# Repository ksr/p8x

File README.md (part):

# P8X — Hand-Built 8-Bit TTL CPU

A from-scratch 8-bit CPU built from ~130 74HCT logic chips on an 8-slot DIN41612 backplane. Fully microcoded; the microcode ROM images burned to the EPROMs are the same images the emulator interprets.

The machine now exists **twice**: as the TTL card set, and as an [FPGA
implementation](fpga/) of the same microarchitecture that boots the same
unmodified monitor, OS and toolchain. Both run the microcode from
`microcode/genucode.py`, and the C emulator is the golden reference for both.

The FPGA build also carries a **PGC-class graphics engine** (480x272
RGB565 panel, hardware 3D transforms, command lists, a fabric-parsed
graphics language modeled on the Matrox PG-640A) — see the
[theory of operation](docs/p8x-graphics-theory.md) and the
[graphics programmer's guide](docs/p8x-graphics-guide.md).

New to the abbreviations and signal names? See [GLOSSARY.md](GLOSSARY.md).

**Who made it:** I designed P8X, and it runs on an FPGA. Claude, Anthropic's AI, has been directly involved in its design, coding and documentation. — Ken Rother

## Architecture

- **8-bit data bus, 16-bit address bus**
- **4 × 16-bit pointer registers** (74169 up/down counters): P0 = PC, P1/P2 = general-purpose, P3 = stack pointer (empty-descending). The address bus is *always* driven by one of these — no separate MAR.
- **Registers:** A, B (ALU operands), T/T2 (hidden microcode temporaries), FLAGS (C, Z, N, V)
- **ALU:** 2 × 74181 + 74182 carry-lookahead, with a post-ALU shifter
- **Microcoded control:** 4 × 28C64 EEPROMs; ROM address = IR | step<<8 | cond<<12; **143 opcodes** defined in `microcode/genucode.py` (256 encodings available)
- **Memory map (rev E):** `$0000–$17FF` ROM (6 KB; shrunk from 8 KB 2026-09-14), `$1800–$FEFF` RAM (2× 62256; $1800–$1FFF is a scratch island), `$FF00–$FFFF` I/O (every data address is single-sourced in [`generators/gen_memmap.py`](generators/gen_memmap.py) → `memmap.inc`/`.h`/`.py`; commands pull the scratch/graphics/TPA-base symbols via `//#use mem`)

## Cards

The TTL machine is six core cards plus a PS/2 input card on the backplane, and a
bus test card for bring-up. Every board is designed and routed in **KiCad** (4-layer;
the plug-in cards are 280 × 140 mm) with orderable Gerbers in `hardware/<board>/kicad/`;
none has been fabricated yet. See [hardware/KICAD-BOARDS.md](hardware/KICAD-BOARDS.md)
and [hardware/RECONCILIATION.md](hardware/RECONCILIATION.md) (build readiness).

| Card | Function |
|------|----------|
| Control / Microcode | Clock, reset, sequencer, microcode EPROMs, IR, condition mux, front-panel |
| Register Bank | P0–P3 16-bit pointer registers, address bus drivers |
| ALU | A, B, T, T2 registers; 74181 ALU; shifter; FLAGS |
| Memory | 28C256 EEPROM (6 KB ROM window) + 2× 62256 SRAM, address decode (rev F) |
| I/O | Switches, LEDs, bus monitor, two 6850 ACIAs (RS-232, two DB9s) |
| CF-IDE | Two CompactFlash drives in 8-bit True IDE mode, at $FF10–$FF17 and $FF18–$FF1F |
| PS/2 | Keyboard + mouse ports at $FF58–$FF5F; an ATmega1284P behind a latch bridge |
| Bus test | Bring-up tool: a Raspberry Pi Pico drives the bus one microcycle at a time over USB |

The cards plug into a passive 8-slot backplane over a 96-pin DIN 41612 bus (rev C2).
The Eagle CAD of the first board generation is frozen (rev E) in each board's
`eagle-deprecated/` directory.

## Toolchain

| Tool | Location | Purpose |
|------|----------|---------|
| `microcode/genucode.py` | `microcode/` | Microcode generator → `u0–u3.bin` EPROM images |
| `assembler/p8xasm.py` | `assembler/` | Two-pass assembler, shares opcode table with genucode.py |
| `emulator/p8xemu.c` | `emulator/` | Cycle-accurate emulator, interprets the same u0–u3.bin images |
| `firmware/p8xmon.asm` | `firmware/` | ROM monitor (E/D/I/F/B/G/? commands) + BIOS jump table at `$0100` |
| `os/p8xos.asm` | `os/` | P8X/OS, RAM-resident disk OS booted from CF ([guide](os/README.md)) |
| `tools/p8xfs.py` | `tools/` | Host-side P8XFS disk-image tool (create/boot/put/get/ls) |
| `basic/p8xbasic.asm` | `basic/` | BASIC interpreter — disk-bootable or run-from-OS builds ([guide](basic/README.md)) |
| `apps/p8xedit.asm`, `apps/p8xasm.asm`, `apps/p8xcc.asm` | `apps/` | On-target toolchain: line editor + native two-pass assembler + native C compiler (`cc`), as `/bin` programs ([guide](apps/README.md)) |
| `compiler/p8cc.py` | `compiler/` | C cross-compiler (subset) → P8X asm → RUNnable `.bin` ([guide](compiler/README.md)) |
| `generators/gen_p8xopc.py` | `generators/` | Opcode table for the native assembler, generated from `genucode.OPC` |
| `generators/gen_eagle.py` | `generators/` | The canonical board netlists (`CARDS`, `busnet()`); its Eagle output is frozen at rev E |
| `generators/gen_kicad.py`, `build.sh` | `generators/` | KiCad boards from those netlists: placement, Freerouting, Gerbers, and the ERC/DRC readiness check |

**Generators are canon.** Never hand-edit board files (`.kicad_pcb`, and the frozen Eagle `.sch`/`.brd`) or ROM binaries — they are build artifacts. Edit the generator and regenerate. See [generators/README.md](generators/README.md) for what each script does and how to run it.

## Quick Start

Setting up a new machine? See [SETUP.md](SETUP.md) for the full toolchain, tier by
tier, and run `python3 tools/setup_check.py` to see what is installed and what each
work area still needs. Only the core-software tier is required to build and test.

```sh
# Build the emulator and regenerate microcode images
cd emulator && make

# Run the smoke tests (message print, JSR/RTS round-trip, branch countdown)
make test

# Rebuild a KiCad board: placement -> Freerouting -> Gerbers + renders -> the
# ERC/gate-sim/DRC/keepout/fab readiness check (needs KiCad 10 and a Freerouting
# jar; `all` builds every board). The netlists come from generators/gen_eagle.py.
cd ..
sh generators/build.sh memory-card
sh generators/check_card.sh memory-card          # the readiness check alone

# Reference PDFs (run from anywhere):
cd hardware
python3 ../generators/gen_bus_pdf.py              # bus definition PDF (hardware/backplane/)
python3 ../microcode/gen_progguide.py             # programmer's guide (-> docs/)
```

### EEPROM / programmer images

Both build paths emit **Intel HEX** alongside the raw `.bin`, for loading into an
EEPROM programmer:

- **Microcode** — `microcode/genucode.py` writes `u0–u3.bin` (what the emulator
  and tests load); the matching Intel HEX for the four 28C64 control-store EPROMs
  is produced into `rom/` by `make rom` (see below).
- **Program ROM** — the assembled monitor + BIOS for the 28C256 at `$0000`
  (about 4.9 KB of the 6 KB window; BASIC is no longer ROM-resident). `make rom` builds it into `rom/`.
- **Any other binary** — `python3 tools/bin2hex.py in.bin out.hex [base]`
  (e.g. a monitor built directly with `p8xasm.py`).

For a ready-to-burn set at fixed paths, run `cd emulator && make rom` (or
`sh tools/build_rom.sh`). It refreshes the four control-store EPROMs in
`microcode/` and writes the program ROM to `rom/p8x-prog-rom.{bin,hex}`. Both
are committed; see [rom/README.md](rom/README.md) for the chip map.

## Documentation

The documents below are also built into the project website, [p8x.cottageworker.com](https://p8x.cottageworker.com) (`website/`, MkDocs; published on every push to `main`).

| Document | Description |
|----------|-------------|
| [hardware/backplane/p8x-bus-definition.md](hardware/backplane/p8x-bus-definition.md) | Authoritative 96-pin bus pinout, signal descriptions, DOE/DLD encoding, microcode word layout |
| [hardware/backplane/p8x-backplane-design.md](hardware/backplane/p8x-backplane-design.md) | PCB stackup, termination analysis, BOM |
| [docs/p8x-card-standards.md](docs/p8x-card-standards.md) | Design rules that apply to every plug-in card |
| [docs/p8x-system-design.md](docs/p8x-system-design.md) | System and card-by-card architecture reference |
| [hardware/cf-card/p8x-cf-os-design.md](hardware/cf-card/p8x-cf-os-design.md) | CF-IDE hardware + P8X/OS design |
| [hardware/cf-card/p8xfs-v2-hierarchical.md](hardware/cf-card/p8xfs-v2-hierarchical.md) | P8XFS v2 hierarchical filesystem spec |
| [docs/p8x-programmers-guide.pdf](docs/p8x-programmers-guide.pdf) | Generated instruction set reference |
| [basic/p8x-basic-guide.md](basic/p8x-basic-guide.md) | P8X BASIC language reference (statements, expressions, graphics, examples) |
| [fpga/README.md](fpga/README.md) | FPGA build: milestones, getting started, both paths |
| [fpga/docs/architecture.md](fpga/docs/architecture.md) | FPGA module hierarchy, peripheral map, graphics, co-sim spec |
| [fpga/rtl/README.md](fpga/rtl/README.md) | What is shared vs sim-only, and the `cen` / `sc_en` contracts |
| [fpga/sim/README.md](fpga/sim/README.md) | How the co-sim trace-diff works, and the graphics frame diff |
| [BACKLOG.md](BACKLOG.md) | Live work only: NEXT / IDEAS / VERIFY / WONT-DO |
| [BACKLOG-DONE.md](BACKLOG-DONE.md) | Completed work + the project log |

### Per-card guides

Each board has its own directory under `hardware/` holding everything about it —
the KiCad board and its Gerbers, placement PDF and renders (`kicad/`), a README
explaining how the circuit works chip by chip, any board-specific design docs, and
the frozen Eagle files (`eagle-deprecated/`):

| Card | Directory |
|------|-----------|
| Control / Microcode | [hardware/control-card/](hardware/control-card/README.md) |
| Register Bank | [hardware/regbank-card/](hardware/regbank-card/README.md) |
| ALU | [hardware/alu-card/](hardware/alu-card/README.md) |
| Memory | [hardware/memory-card/](hardware/memory-card/README.md) |
| I/O | [hardware/io-card/](hardware/io-card/README.md) |
| CF-IDE | [hardware/cf-card/](hardware/cf-card/README.md) |
| PS/2 | [hardware/ps2-card/](hardware/ps2-card/README.md) |
| Bus test | [hardware/bustest-card/](hardware/bustest-card/p8x-bustest-card-design.md) |
| Backplane | [hardware/backplane/](hardware/backplane/p8x-backplane-design.md) |

## FPGA implementation

A standalone [FPGA build](fpga/) on a **Sipeed Tang Nano 20K** (Gowin GW2AR-18)
runs the whole machine — CPU, memory, ACIA console, microSD disk, and a 4.3"
480x272 graphics panel — from one chip and a USB cable. It is a **parallel track to the TTL build, not a replacement**:
same horizontal microcode word, same sequencer, same pointer/address model, so
the monitor, OS, BASIC, C compiler and assembler run **unmodified**.

| Milestone | State |
|-----------|-------|
| 0 First light (UART echo + heartbeat) | done |
| 1 CPU core in simulation, all 88 opcodes of the time | done |
| 2 ACIA + driven console in simulation | done |
| 3 Core on real hardware, full 64K map | done |
| 4 microSD disk — P8X/OS boots from card | done |
| 5 Clock-up + IRQ | next |
| 6 Graphics: 480x272 panel + drawing engine | done |

As built: **9 MHz** effective (27 MHz fabric, three phases per microcycle). The
CPU-only build is 40/46 block RAMs at ~48 MHz Fmax; adding the graphics panel takes
it to 44/46 and 13288/20736 LUT4, with Fmax measured at 38.8 MHz — still four times
the clock it runs at. P8X is programmed into the board's flash, so it comes up
standalone on power.

**Graphics** (`build.sh lcd`) adds the panel's native 480×272 framebuffer in
**RGB565 direct colour** — a pixel IS its colour, 65,536 of them — living in
the Tang Nano's in-package SDRAM behind a streaming controller, with a drawing
engine driven by BASIC in one window-space coordinate system (y up, the
PGC's own): `COLOR r,g,b` (or one packed value), `CLS`, `PIXELW`, `LINE`,
`BOX`, `CIRCLE` (a second radius gives an ellipse), `IMAGE` (draws a
P8I picture file — `tools/p8img.py` converts anything into one), the
`PIXELR(x,y)` and `RGB(r,g,b)` functions — plus the full PGC graphics
language as native statements (`MOVE`/`DRAW`/`POLY`/`RECT`, matrices, 3D,
command lists; see `man basic`). Text is the PGC's own stroke `TEXT`,
drawn card-side from the font the OS streams from `/FONT.GL` at boot
(GTEXT and its software rasterizer retired 2026-09-01). The drawing
statements emit that language; the engine lives in the device, so a
filled box costs the same handful of instructions as an empty one.
There is one geometry and no modes or palette to manage.
The same device is modelled in `p8xemu`, and the two are byte-compared frame
by frame.

**3D** (stages 7–8, `fpga/tang-nano-20k/sdram/STAGE*.md`): a wireframe
pipeline available three ways from C — all in software (`//#use gfx` +
`//#use g3d`), accelerated by the **MDU** (a memory-mapped hardware
multiply-divide unit at `$FF30`), or fully in fabric via the **geometry
engine** (`$FF40`): edge lists in SDRAM, an S7.8 matrix, one command to
transform/clip/project/draw, and page-flipped double buffering. The same
program picks the fastest fitted path at runtime; `cube` on the shipped disk
demonstrates all of them (`man cube`, `man g3d`).

**Verification is the point.** Every milestone is "make the RTL match the
emulator": the same program runs on both and their per-cycle architectural state
is diffed, so a divergence is a bug with an exact microcycle and signal rather
than a mystery. `fpga/sim/isa_test.asm` drives the original 88 opcodes through that diff;
the 55 added since are microcode only (no new hardware), and the RTL runs them from
the same images.

```sh
fpga/sim/run.sh 60000 isa_test.asm          # co-sim, the original 88 opcodes
fpga/sim/console.sh "" os/run-disk.img      # interactive console on the RTL
fpga/tang-nano-20k/build.sh cpu load        # build + program the board
```

## Status

- Emulator working: 143 opcodes, ACIA on stdin/stdout, CF-IDE disk model (`-c `), interactive I/O card (switches `-s`, LED trace `-L`), verified against microcode images
- Assembler working: two-pass, full expression support, shares opcode table with microcode generator
- KiCad boards designed and routed for the six CPU cards, the PS/2 card, the bus test card and the backplane (9 boards, 0 unconnected, Gerbers in each `kicad/`); none fabricated yet. The Eagle files of the first generation are frozen in `eagle-deprecated/`. (The standalone LED test card was a CAD-workflow trial, never built — deprecated and moved to `hardware/deprecated/led-card/`; its I/O address `$FF0C` is now free.)
- ROM monitor boots in the emulator; its filesystem hooks (`I`/`F`/`B`) run end to end against a CF image (`make test-cf`)
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
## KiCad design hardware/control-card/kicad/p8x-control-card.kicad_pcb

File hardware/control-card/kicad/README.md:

# control-card -- KiCad

Generated by `generators/gen_kicad.py` from the canonical gen_eagle netlist
(`CARDS["control-card"]`), same standard as the memory card: 4-layer (F/B signals,
In1=GND, In2=VCC planes), a bypass cap above each IC, a labelled LED/jumper bank,
part values on silk. Routed with Freerouting. GENERATORS ARE CANON -- edit
`gen_kicad.py` and re-run `generators/build_kicad_card.sh control-card`.

| File | What |
|------|------|
| `p8x-control-card.kicad_pcb` | the board |
| `p8x-control-card.ses` | the Freerouting routing |
| `p8x-control-card-gerbers.zip` | orderable gerbers |
| `p8x-control-card-placement.pdf` | parts placement (refs+values) |
| `p8x-control-card-render-top.png` / `-3d.png` | renders |

Exotic parts use the closest standard KiCad footprint (flagged when built).

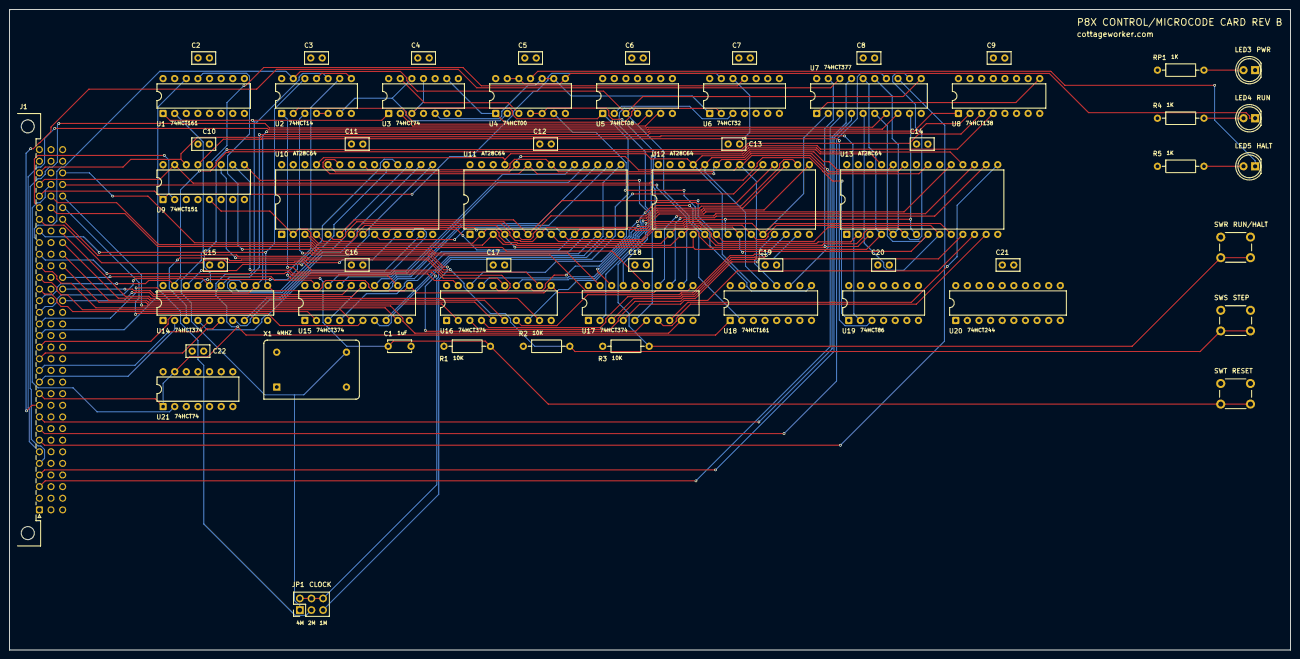
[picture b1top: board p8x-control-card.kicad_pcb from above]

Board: 4 copper layers, 280.0 x 140.0 mm, 58 parts (0 on the bottom side), 120 nets.

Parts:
C1: 1uF; C_Disc_D5.0mm_W2.5mm_P5.00mm
C2, C3, C4, C5, C6, C7, C8, C9, C10, C11, C12, C13, C14, C15, C16, C17, C18, C19, C20, C21, C22: 100nF; C_Disc_D5.0mm_W2.5mm_P2.50mm
J1: MABC96R; DIN41612_C_3x32_Male_Horizontal_THT
JP1: CLKSEL; PinHeader_2x03_P2.54mm_Vertical
LED3, LED4: GRN; LED_D5.0mm
LED5: RED; LED_D5.0mm
R1, R2, R3: 10K; R_Axial_DIN0207_L6.3mm_D2.5mm_P10.16mm_Horizontal
R4, R5: 1K; R_Axial_DIN0207_L6.3mm_D2.5mm_P10.16mm_Horizontal
RP1: 1K; R_Axial_DIN0207_L6.3mm_D2.5mm_P10.16mm_Horizontal
SWR: SPST; SW_PUSH_6mm
SWS: SPST; SW_PUSH_6mm
SWT: SPST; SW_PUSH_6mm
U1, U18: 74HCT161; DIP-16_W7.62mm
U2: 74HCT14; DIP-14_W7.62mm
U3, U21: 74HCT74; DIP-14_W7.62mm
U4: 74HCT00; DIP-14_W7.62mm
U5: 74HCT08; DIP-14_W7.62mm
U6: 74HCT32; DIP-14_W7.62mm
U7: 74HCT377; DIP-20_W7.62mm
U8: 74HCT138; DIP-16_W7.62mm
U9: 74HCT151; DIP-16_W7.62mm
U10, U11, U12, U13: 28C64; DIP-28_W15.24mm
U14, U15, U16, U17: 74HCT374; DIP-20_W7.62mm
U19: 74HCT86; DIP-14_W7.62mm
U20: 74HCT244; DIP-20_W7.62mm
X1: 4MHZ; Oscillator_DIP-14

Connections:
-IRLD: U7.1, U8.9
-RES: J1.a11, U1.1, U2.10, U3.1, U18.1, U21.1, U21.13
-USTL: U4.6, U18.9
ALUM: J1.c23, U16.5
ALUS0: J1.c19, U15.15
ALUS1: J1.c20, U15.16
ALUS2: J1.c21, U15.19
ALUS3: J1.c22, U16.2
BSEL: J1.b28, U17.19
CIN: J1.c24, U16.6
CLK: J1.a24, U2.13, U5.3, U7.11, U18.2
CLKB: J1.a25, U2.12, U14.11, U15.11, U16.11, U17.11
CLKEN: U5.2, U6.3
CLKRAW: JP1.2, JP1.4, JP1.6, U3.3, U3.11, U5.1
CLRC: J1.b27, U17.16
CONDY: U9.5, U10.2, U11.2, U12.2, U13.2
D0: J1.a3, U7.3
D1: J1.a4, U7.4
D2: J1.a5, U7.7
D3: J1.a6, U7.8
D4: J1.a7, U7.13
D5: J1.a8, U7.14
D6: J1.a9, U7.17
D7: J1.a10, U7.18
DIVQA: JP1.3, U1.14
DIVQB: JP1.5, U1.13
DLD0: J1.a16, U8.1, U14.12
DLD1: J1.a17, U8.2, U14.15
DLD2: J1.a18, U8.3, U14.16
DLD3: J1.a19, U8.4, U14.19
DOE0: J1.a12, U14.2
DOE1: J1.a13, U14.5
DOE2: J1.a14, U14.6
DOE3: J1.a15, U14.9
FC: J1.a27, U9.2
FCOND0: U9.11, U16.16
FCOND1: U9.10, U16.19
FCOND2: U9.9, U17.2
FN: J1.a29, U9.15, U19.1
FV: J1.a30, U9.14, U19.2
FZ: J1.a28, U6.13, U9.1
GND: C1.2, C2.2, C3.2, C4.2, C5.2, C6.2, C7.2, C8.2, C9.2, C10.2, C11.2, C12.2, C13.2, C14.2, C15.2, C16.2, C17.2, C18.2, C19.2, C20.2, C21.2, C22.2, J1.a31, J1.a32, J1.b3, J1.b5, J1.b7, J1.b9, J1.b11, J1.b13, J1.b15, J1.b17, J1.b19, J1.b21, J1.b23, J1.b25, J1.b31, J1.b32, J1.c31, J1.c32, LED3.1, SWR.1, SWS.1, SWT.1, U1.3, U1.4, U1.5, U1.6, U1.8, U2.7, U3.7, U4.7, U5.7, U5.9, U5.10, U5.12, U5.13, U6.4, U6.5, U6.7, U6.9, U6.10, U7.10, U8.5, U8.8, U9.4, U9.7, U9.8, U10.14, U10.20, U10.22, U11.14, U11.20, U11.22, U12.14, U12.20, U12.22, U13.14, U13.20, U13.22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
HALT: U2.1, U17.6
HALTK: LED5.1, U4.11
HALTN: U2.2, U5.5
IRQ: J1.b29, U21.2
IRQ0: U7.2, U10.10, U11.10, U12.10, U13.10
IRQ1: U7.5, U10.9, U11.9, U12.9, U13.9
IRQ2: U7.6, U10.8, U11.8, U12.8, U13.8
IRQ3: U7.9, U10.7, U11.7, U12.7, U13.7
IRQ4: U7.12, U10.6, U11.6, U12.6, U13.6
IRQ5: U7.15, U10.5, U11.5, U12.5, U13.5
IRQ6: U7.16, U10.4, U11.4, U12.4, U13.4
IRQ7: U7.19, U10.3, U11.3, U12.3, U13.3
LDF: J1.a26, U16.15
LDZN: J1.c28, U17.9
LEDHL: LED5.2, R5.2
LEDP: LED3.2, RP1.2
LEDRN: LED4.2, R4.2
NV: U6.12, U9.13, U19.3
NVZ: U6.11, U9.12
OSCO: JP1.1, U1.2, X1.8
P14B0: U10.11, U14.3
P14B1: U10.12, U14.4
P14B2: U10.13, U14.7
P14B3: U10.15, U14.8
P14B4: U10.16, U14.13
P14B5: U10.17, U14.14
P14B6: U10.18, U14.17
P14B7: U10.19, U14.18
P15B0: U11.11, U15.3
P15B1: U11.12, U15.4
P15B2: U11.13, U15.7
P15B3: U11.15, U15.8
P15B4: U11.16, U15.13
P15B5: U11.17, U15.14
P15B6: U11.18, U15.17
P15B7: U11.19, U15.18
P16B0: U12.11, U16.3
P16B1: U12.12, U16.4
P16B2: U12.13, U16.7
P16B3: U12.15, U16.8
P16B4: U12.16, U16.13
P16B5: U12.17, U16.14
P16B6: U12.18, U16.17
P16B7: U12.19, U16.18
P17B0: U13.11, U17.3
P17B1: U13.12, U17.4
P17B2: U13.13, U17.7
P17B3: U13.15, U17.8
P17B4: U13.16, U17.13
P17B5: U13.17, U17.14
P17B6: U13.18, U17.17
P17B7: U13.19, U17.18
PDEC: J1.a23, U15.12
PINC: J1.a22, U15.9
PSEL0: J1.a20, U15.2
PSEL1: J1.a21, U15.5
PSEL2: J1.c27, U15.6
RSTP: U2.8, U2.11
RSTRAW: C1.1, R1.2, SWT.2, U2.9
RUND: U3.2, U5.6
RUNLK: LED4.1, U4.8, U4.12, U4.13
RUNQ: U3.5, U4.9, U4.10, U6.1
RUNSW: R3.2, SWR.2, U5.4
SETC: J1.c30, U17.15
SH0: J1.c25, U16.9
SH1: J1.c26, U16.12
SHCIN: J1.c29, U17.12
SQ0: U10.25, U11.25, U12.25, U13.25, U18.14
SQ1: U10.24, U11.24, U12.24, U13.24, U18.13
SQ2: U10.21, U11.21, U12.21, U13.21, U18.12
SQ3: U10.23, U11.23, U12.23, U13.23, U18.11
STEPCLR: U3.13, U4.3
STEPN: U2.4, U2.5
STEPP: U2.6, U3.12, U4.2
STEPQ: U3.9, U4.1, U6.2
STEPRAW: R2.2, SWS.2, U2.3
URST: U4.4, U4.5, U17.5
VCC: C2.1, C3.1, C4.1, C5.1, C6.1, C7.1, C8.1, C9.1, C10.1, C11.1, C12.1, C13.1, C14.1, C15.1, C16.1, C17.1, C18.1, C19.1, C20.1, C21.1, C22.1, J1.a1, J1.a2, J1.b1, J1.b2, J1.c1, J1.c2, R1.1, R2.1, R3.1, R4.1, R5.1, RP1.1, U1.7, U1.9, U1.10, U1.16, U2.14, U3.4, U3.10, U3.14, U4.14, U5.14, U6.14, U7.20, U8.6, U8.16, U9.3, U9.16, U10.27, U10.28, U11.27, U11.28, U12.27, U12.28, U13.27, U13.28, U14.20, U15.20, U16.20, U17.20, U18.7, U18.10, U18.16, U19.14, U20.1, U20.8, U20.19, U20.20, U21.4, U21.10, U21.14, X1.14

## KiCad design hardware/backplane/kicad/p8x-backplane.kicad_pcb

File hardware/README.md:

# hardware/

The physical machine: one passive backplane, six plug-in CPU cards, a PS/2 input
card, and a bus test card for bring-up. Each board has its own directory holding a
chip-by-chip README, a theory of operation or design doc, and the **KiCad** board
(`kicad/`: the `.kicad_pcb`, the Freerouting session, orderable Gerbers, a
placement PDF and renders). Every board is designed and routed; none has been
fabricated yet. Board status: **[KICAD-BOARDS.md](KICAD-BOARDS.md)**; build
readiness against the emulator and the FPGA: **[RECONCILIATION.md](RECONCILIATION.md)**.

| Board | Directory | Function |
|-------|-----------|----------|
| Control / Microcode | [control-card/](control-card/README.md) | Clock, reset, sequencer, microcode EPROMs, IR, condition mux, front panel |
| Register Bank | [regbank-card/](regbank-card/README.md) | P0–P3 16-bit pointer registers, address-bus drivers |
| ALU | [alu-card/](alu-card/README.md) | A/B/T/T2 registers, 74181 ALU, shifter, FLAGS |
| Memory | [memory-card/](memory-card/README.md) | 28C256 ROM (6 KB window, `$0000–$17FF`) + 2× 62256 SRAM, address decode (rev F) |
| I/O | [io-card/](io-card/README.md) | Switches, LEDs, bus monitor, two 6850 ACIAs (`$FF04/05`, `$FF08/09`) with two DB9s (rev B) |
| CF-IDE | [cf-card/](cf-card/README.md) | Two CompactFlash drives in 8-bit True IDE mode: `$FF10–$FF17` and `$FF18–$FF1F` (rev B) |
| PS/2 | [ps2-card/](ps2-card/README.md) | Keyboard + mouse at `$FF58–$FF5F`: an ATmega1284P behind a latch bridge (rev A) |
| Bus test | [bustest-card/](bustest-card/p8x-bustest-card-design.md) | Bring-up tool: a Raspberry Pi Pico drives the bus over USB, one microcycle at a time |
| Backplane | [backplane/](backplane/p8x-backplane-design.md) | 8-slot passive 96-pin DIN 41612 bus (rev C2), 262 × 128 mm |

The plug-in cards are all 280 × 140 mm, 4-layer (signals on the outer layers, GND
and +5 V planes inside).

**Eagle (frozen).** The first board generation was drawn in Eagle/Fusion from
`generators/gen_eagle.py`. On 2026-09-18 the KiCad flow replaced it: each board's
Eagle `.sch`/`.brd` and its schematic and placement PDFs moved to
`<board>/eagle-deprecated/`, frozen at rev E, and are no longer maintained (the
Eagle memory card still carries the old 8 KB ROM decode; the KiCad rev F board has
the 6 KB one). `gen_eagle.py` stays the source of the netlists.

> **Deprecated:** the standalone **LED test card** (a write-only 8-LED output
> latch that decoded `$FF0C`) was a CAD-workflow trial, never built. It has been
> moved to [`deprecated/led-card/`](deprecated/led-card/) and its I/O address
> `$FF0C` is now free. (This is unrelated to the `$FF02` LED latch the emulator
> traces, which stays.) The combined I/O + CF + PS/2 **peripheral card** is parked
> in `parked/peripheral-card/` (2026-09-19); the design went back to three cards.

### Not yet realised as TTL boards
See **[RECONCILIATION.md](RECONCILIATION.md)** for the full board-vs-emulator/FPGA
build-readiness pass. Subsystems the emulator and/or the FPGA already provide that
have **no TTL card** yet:

| Subsystem | Where it lives now | TTL board |
|-----------|--------------------|-----------|
| MDU multiply/divide (`$FF30–$FF3F`) | emulator model + FPGA (`mdu_core.v`) | none yet |
| Graphics-language port (`$FF50–$FF54`) | emulator model + the Tang Nano 20K graphics card | none (the FPGA card *is* the graphics engine) |
| IRQ controller (`$FF06` device-IRQ model) | emulator model | none yet — the next card to design |

**[assembly/](assembly/README.md)** — 3D renders of the assembled machine: the
backplane with all eight cards standing in their slots, each card populated
(rendered from the boards by `generators/render_assembly.py`; slot order inside).

`p8x-bom.csv` — the orderable bill of materials for the whole machine
(ICs, sockets, connectors, passives), generated by
[`../generators/gen_bom.py`](../generators/).

## Rebuilding boards

**Generators are canon** — never hand-edit a `.kicad_pcb`. The netlists live in
[`../generators/gen_eagle.py`](../generators/) (`CARDS`, `busnet()`);
`gen_kicad.py` turns a card into a placed KiCad board (the memory, I/O, CF, PS/2
cards and the backplane have bespoke placement scripts in their `kicad/`
directories), Freerouting routes it, and `check_card.sh` runs the readiness check
(ERC, gate-level simulation where a testbench exists, DRC, mounting-hole keepout,
fab minimums). One command does all of it, from the repository root:

```sh
sh generators/build.sh memory-card      # one board (or: all)
sh generators/check_card.sh memory-card # the readiness check alone
```

It needs KiCad 10 and a Freerouting jar. See
[../generators/README.md](../generators/README.md) for the scripts and
[../docs/p8x-card-standards.md](../docs/p8x-card-standards.md) for the rules
every card follows.

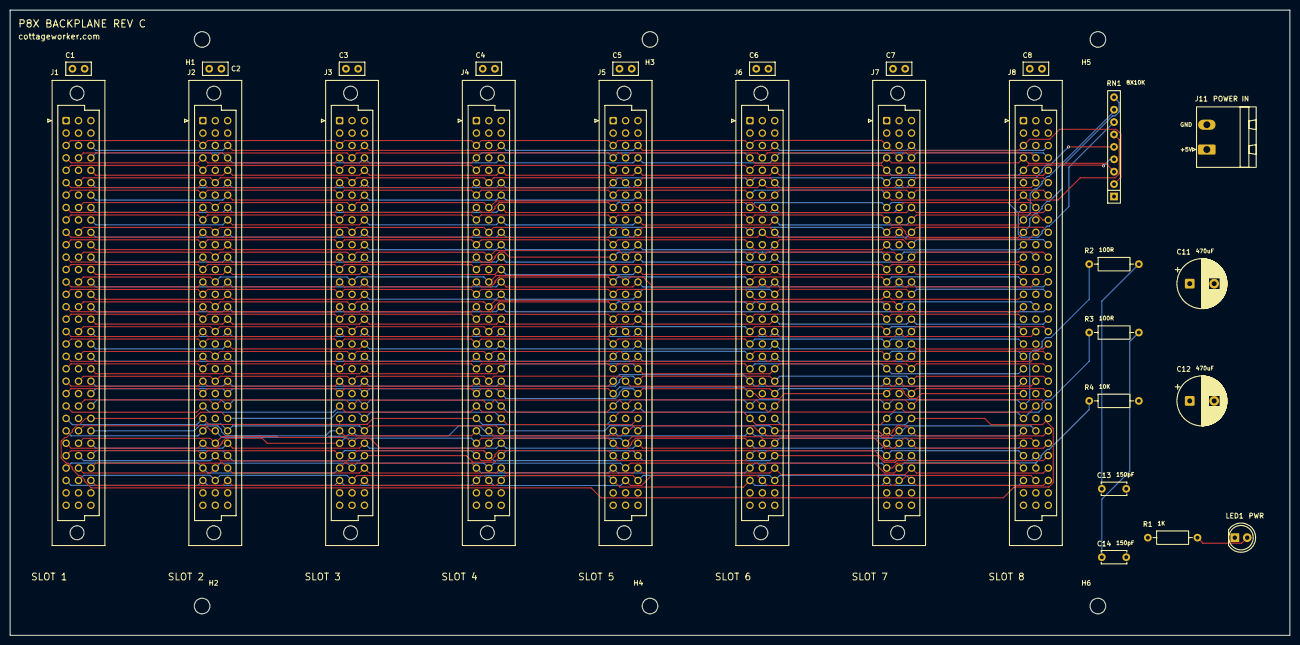
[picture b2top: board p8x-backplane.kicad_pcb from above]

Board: 4 copper layers, 262.0 x 128.0 mm, 33 parts (0 on the bottom side), 77 nets.

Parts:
C1, C2, C3, C4, C5, C6, C7, C8: 100nF; C_Disc_D5.0mm_W2.5mm_P2.50mm
C11, C12: 470uF; CP_Radial_D10.0mm_P5.00mm
C13, C14: 150pF; C_Disc_D5.0mm_W2.5mm_P5.00mm
H1, H2, H3, H4, H5, H6: MountingHole_3.2mm_M3
J1: SLOT1; DIN41612_C_3x32_Female_Vertical_THT
J2: SLOT2; DIN41612_C_3x32_Female_Vertical_THT
J3: SLOT3; DIN41612_C_3x32_Female_Vertical_THT
J4: SLOT4; DIN41612_C_3x32_Female_Vertical_THT
J5: SLOT5; DIN41612_C_3x32_Female_Vertical_THT
J6: SLOT6; DIN41612_C_3x32_Female_Vertical_THT
J7: SLOT7; DIN41612_C_3x32_Female_Vertical_THT
J8: SLOT8; DIN41612_C_3x32_Female_Vertical_THT
J11: PWR-5V; PhoenixContact_MSTBA_2,5_2-G-5,08_1x02_P5.08mm_Horizontal
LED1: PWR; LED_D5.0mm
R1: 1K; R_Axial_DIN0207_L6.3mm_D2.5mm_P10.16mm_Horizontal
R2, R3: 100R; R_Axial_DIN0207_L6.3mm_D2.5mm_P10.16mm_Horizontal
R4: 10K; R_Axial_DIN0207_L6.3mm_D2.5mm_P10.16mm_Horizontal
RN1: 8X10K; R_Array_SIP9

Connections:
-RES: J1.a11, J2.a11, J3.a11, J4.a11, J5.a11, J6.a11, J7.a11, J8.a11
A0: J1.c3, J2.c3, J3.c3, J4.c3, J5.c3, J6.c3, J7.c3, J8.c3
A1: J1.c4, J2.c4, J3.c4, J4.c4, J5.c4, J6.c4, J7.c4, J8.c4
A2: J1.c5, J2.c5, J3.c5, J4.c5, J5.c5, J6.c5, J7.c5, J8.c5
A3: J1.c6, J2.c6, J3.c6, J4.c6, J5.c6, J6.c6, J7.c6, J8.c6
A4: J1.c7, J2.c7, J3.c7, J4.c7, J5.c7, J6.c7, J7.c7, J8.c7
A5: J1.c8, J2.c8, J3.c8, J4.c8, J5.c8, J6.c8, J7.c8, J8.c8
A6: J1.c9, J2.c9, J3.c9, J4.c9, J5.c9, J6.c9, J7.c9, J8.c9
A7: J1.c10, J2.c10, J3.c10, J4.c10, J5.c10, J6.c10, J7.c10, J8.c10
A8: J1.c11, J2.c11, J3.c11, J4.c11, J5.c11, J6.c11, J7.c11, J8.c11
A9: J1.c12, J2.c12, J3.c12, J4.c12, J5.c12, J6.c12, J7.c12, J8.c12
A10: J1.c13, J2.c13, J3.c13, J4.c13, J5.c13, J6.c13, J7.c13, J8.c13
A11: J1.c14, J2.c14, J3.c14, J4.c14, J5.c14, J6.c14, J7.c14, J8.c14
A12: J1.c15, J2.c15, J3.c15, J4.c15, J5.c15, J6.c15, J7.c15, J8.c15
A13: J1.c16, J2.c16, J3.c16, J4.c16, J5.c16, J6.c16, J7.c16, J8.c16
A14: J1.c17, J2.c17, J3.c17, J4.c17, J5.c17, J6.c17, J7.c17, J8.c17
A15: J1.c18, J2.c18, J3.c18, J4.c18, J5.c18, J6.c18, J7.c18, J8.c18
ALUM: J1.c23, J2.c23, J3.c23, J4.c23, J5.c23, J6.c23, J7.c23, J8.c23
ALUS0: J1.c19, J2.c19, J3.c19, J4.c19, J5.c19, J6.c19, J7.c19, J8.c19
ALUS1: J1.c20, J2.c20, J3.c20, J4.c20, J5.c20, J6.c20, J7.c20, J8.c20
ALUS2: J1.c21, J2.c21, J3.c21, J4.c21, J5.c21, J6.c21, J7.c21, J8.c21
ALUS3: J1.c22, J2.c22, J3.c22, J4.c22, J5.c22, J6.c22, J7.c22, J8.c22
BSEL: J1.b28, J2.b28, J3.b28, J4.b28, J5.b28, J6.b28, J7.b28, J8.b28
CIN: J1.c24, J2.c24, J3.c24, J4.c24, J5.c24, J6.c24, J7.c24, J8.c24
CLK: J1.a24, J2.a24, J3.a24, J4.a24, J5.a24, J6.a24, J7.a24, J8.a24, R2.1
CLKB: J1.a25, J2.a25, J3.a25, J4.a25, J5.a25, J6.a25, J7.a25, J8.a25, R3.1
CLKB_T: C14.1, R3.2
CLK_T: C13.1, R2.2
CLRC: J1.b27, J2.b27, J3.b27, J4.b27, J5.b27, J6.b27, J7.b27, J8.b27
D0: J1.a3, J2.a3, J3.a3, J4.a3, J5.a3, J6.a3, J7.a3, J8.a3, RN1.2
D1: J1.a4, J2.a4, J3.a4, J4.a4, J5.a4, J6.a4, J7.a4, J8.a4, RN1.3
D2: J1.a5, J2.a5, J3.a5, J4.a5, J5.a5, J6.a5, J7.a5, J8.a5, RN1.4
D3: J1.a6, J2.a6, J3.a6, J4.a6, J5.a6, J6.a6, J7.a6, J8.a6, RN1.5
D4: J1.a7, J2.a7, J3.a7, J4.a7, J5.a7, J6.a7, J7.a7, J8.a7, RN1.6
D5: J1.a8, J2.a8, J3.a8, J4.a8, J5.a8, J6.a8, J7.a8, J8.a8, RN1.7
D6: J1.a9, J2.a9, J3.a9, J4.a9, J5.a9, J6.a9, J7.a9, J8.a9, RN1.8
D7: J1.a10, J2.a10, J3.a10, J4.a10, J5.a10, J6.a10, J7.a10, J8.a10, RN1.9
DLD0: J1.a16, J2.a16, J3.a16, J4.a16, J5.a16, J6.a16, J7.a16, J8.a16
DLD1: J1.a17, J2.a17, J3.a17, J4.a17, J5.a17, J6.a17, J7.a17, J8.a17
DLD2: J1.a18, J2.a18, J3.a18, J4.a18, J5.a18, J6.a18, J7.a18, J8.a18
DLD3: J1.a19, J2.a19, J3.a19, J4.a19, J5.a19, J6.a19, J7.a19, J8.a19
DOE0: J1.a12, J2.a12, J3.a12, J4.a12, J5.a12, J6.a12, J7.a12, J8.a12
DOE1: J1.a13, J2.a13, J3.a13, J4.a13, J5.a13, J6.a13, J7.a13, J8.a13
DOE2: J1.a14, J2.a14, J3.a14, J4.a14, J5.a14, J6.a14, J7.a14, J8.a14
DOE3: J1.a15, J2.a15, J3.a15, J4.a15, J5.a15, J6.a15, J7.a15, J8.a15
FC: J1.a27, J2.a27, J3.a27, J4.a27, J5.a27, J6.a27, J7.a27, J8.a27
FN: J1.a29, J2.a29, J3.a29, J4.a29, J5.a29, J6.a29, J7.a29, J8.a29
FV: J1.a30, J2.a30, J3.a30, J4.a30, J5.a30, J6.a30, J7.a30, J8.a30
FZ: J1.a28, J2.a28, J3.a28, J4.a28, J5.a28, J6.a28, J7.a28, J8.a28
GND: C1.2, C2.2, C3.2, C4.2, C5.2, C6.2, C7.2, C8.2, C11.2, C12.2, C13.2, C14.2, J1.a31, J1.a32, J1.b3, J1.b5, J1.b7, J1.b9, J1.b11, J1.b13, J1.b15, J1.b17, J1.b19, J1.b21, J1.b23, J1.b25, J1.b31, J1.b32, J1.c31, J1.c32, J2.a31, J2.a32, J2.b3, J2.b5, J2.b7, J2.b9, J2.b11, J2.b13, J2.b15, J2.b17, J2.b19, J2.b21, J2.b23, J2.b25, J2.b31, J2.b32, J2.c31, J2.c32, J3.a31, J3.a32, J3.b3, J3.b5, J3.b7, J3.b9, J3.b11, J3.b13, J3.b15, J3.b17, J3.b19, J3.b21, J3.b23, J3.b25, J3.b31, J3.b32, J3.c31, J3.c32, J4.a31, J4.a32, J4.b3, J4.b5, J4.b7, J4.b9, J4.b11, J4.b13, J4.b15, J4.b17, J4.b19, J4.b21, J4.b23, J4.b25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
IRQ: J1.b29, J2.b29, J3.b29, J4.b29, J5.b29, J6.b29, J7.b29, J8.b29, R4.1
LDF: J1.a26, J2.a26, J3.a26, J4.a26, J5.a26, J6.a26, J7.a26, J8.a26
LDZN: J1.c28, J2.c28, J3.c28, J4.c28, J5.c28, J6.c28, J7.c28, J8.c28
LED_A: LED1.2, R1.2
PDEC: J1.a23, J2.a23, J3.a23, J4.a23, J5.a23, J6.a23, J7.a23, J8.a23
PINC: J1.a22, J2.a22, J3.a22, J4.a22, J5.a22, J6.a22, J7.a22, J8.a22
PSEL0: J1.a20, J2.a20, J3.a20, J4.a20, J5.a20, J6.a20, J7.a20, J8.a20
PSEL1: J1.a21, J2.a21, J3.a21, J4.a21, J5.a21, J6.a21, J7.a21, J8.a21
PSEL2: J1.c27, J2.c27, J3.c27, J4.c27, J5.c27, J6.c27, J7.c27, J8.c27
SETC: J1.c30, J2.c30, J3.c30, J4.c30, J5.c30, J6.c30, J7.c30, J8.c30
SH0: J1.c25, J2.c25, J3.c25, J4.c25, J5.c25, J6.c25, J7.c25, J8.c25
SH1: J1.c26, J2.c26, J3.c26, J4.c26, J5.c26, J6.c26, J7.c26, J8.c26
SHCIN: J1.c29, J2.c29, J3.c29, J4.c29, J5.c29, J6.c29, J7.c29, J8.c29
SPARE11: J1.b30, J2.b30, J3.b30, J4.b30, J5.b30, J6.b30, J7.b30, J8.b30
SPARE12: J1.b4, J2.b4, J3.b4, J4.b4, J5.b4, J6.b4, J7.b4, J8.b4
SPARE13: J1.b6, J2.b6, J3.b6, J4.b6, J5.b6, J6.b6, J7.b6, J8.b6
SPARE14: J1.b8, J2.b8, J3.b8, J4.b8, J5.b8, J6.b8, J7.b8, J8.b8
SPARE15: J1.b10, J2.b10, J3.b10, J4.b10, J5.b10, J6.b10, J7.b10, J8.b10
SPARE16: J1.b12, J2.b12, J3.b12, J4.b12, J5.b12, J6.b12, J7.b12, J8.b12
SPARE17: J1.b14, J2.b14, J3.b14, J4.b14, J5.b14, J6.b14, J7.b14, J8.b14
SPARE18: J1.b16, J2.b16, J3.b16, J4.b16, J5.b16, J6.b16, J7.b16, J8.b16
SPARE19: J1.b18, J2.b18, J3.b18, J4.b18, J5.b18, J6.b18, J7.b18, J8.b18
SPARE20: J1.b20, J2.b20, J3.b20, J4.b20, J5.b20, J6.b20, J7.b20, J8.b20
SPARE21: J1.b22, J2.b22, J3.b22, J4.b22, J5.b22, J6.b22, J7.b22, J8.b22
SPARE22: J1.b24, J2.b24, J3.b24, J4.b24, J5.b24, J6.b24, J7.b24, J8.b24
SPARE23: J1.b26, J2.b26, J3.b26, J4.b26, J5.b26, J6.b26, J7.b26, J8.b26
VCC: C1.1, C2.1, C3.1, C4.1, C5.1, C6.1, C7.1, C8.1, C11.1, C12.1, J1.a1, J1.a2, J1.b1, J1.b2, J1.c1, J1.c2, J2.a1, J2.a2, J2.b1, J2.b2, J2.c1, J2.c2, J3.a1, J3.a2, J3.b1, J3.b2, J3.c1, J3.c2, J4.a1, J4.a2, J4.b1, J4.b2, J4.c1, J4.c2, J5.a1, J5.a2, J5.b1, J5.b2, J5.c1, J5.c2, J6.a1, J6.a2, J6.b1, J6.b2, J6.c1, J6.c2, J7.a1, J7.a2, J7.b1, J7.b2, J7.c1, J7.c2, J8.a1, J8.a2, J8.b1, J8.b2, J8.c1, J8.c2, J11.1, R1.1, R4.2, RN1.1

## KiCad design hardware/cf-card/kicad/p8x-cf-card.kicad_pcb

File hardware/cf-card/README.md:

# CF-IDE Card

> **Theory of operation:** [p8x-cf-card-theory.md](p8x-cf-card-theory.md) — deep walkthrough of inputs/outputs, signal flow, and logic.

Adds mass storage: a CompactFlash card running in **8-bit True IDE mode**,
memory-mapped into the I/O page at **$FF10–$FF17**. This is what lets the P8X load
an OS and a filesystem from removable media instead of living entirely in ROM.

> **Rev B (2026-09-19): two drives.** The routed KiCad board in
> [`kicad/`](kicad/README.md) (not yet fabricated) carries a second, fully decoded
> CF drive: drive 0 at `$FF10–$FF17` on header J2, drive 1 at `$FF18–$FF1F` on
> header J5, each with its own 74245 buffer, strobe glue, pull-ups and activity
> LED (master/slave on one channel was rejected as unreliable for True IDE CF).
> **Software follow-up:** the firmware CF driver and the emulator select drive 1
> with the device bit on `$FF10–$FF17`, so drive 1 on this card needs a
> drive-selectable port base first; drive 0 works unchanged. The chip-by-chip text
> below describes the drive-0 circuit.

> This README describes the circuit as actually built in
> [`generators/gen_eagle.py`](../../generators/gen_eagle.py). For the storage
> software stack see [p8x-cf-os-design.md](p8x-cf-os-design.md) and
> [p8xfs-v2-hierarchical.md](p8xfs-v2-hierarchical.md); for bus pins see
> [p8x-bus-definition.md](../backplane/p8x-bus-definition.md).

## Chip inventory

| Ref | Device | Role |
|-----|--------|------|
| U1 | 74245 | Bidirectional data-bus transceiver (P8X bus ↔ CF data) |
| U2 | 7430 | 8-input NAND — I/O page ($FFxx) detector |
| U3 | 74138 | DOE decoder (read enable) |
| U4 | 74138 | DLD decoder (write strobe) |
| U5 | 74HCT14 | Schmitt inverters — strobe/select conditioning |
| U6, U7 | 7410 | 3-input NAND — register/select decode and -IOR/-IOW gating |
| U8 | 74HCT08 | AND glue — chip-select combine, activity LED |
| J2 | 40-pin IDE | CompactFlash / IDE connector |

## How it works

### Address decode ($FF10–$FF17)
U2 (7430) detects the `$FFxx` page. The CF task-file registers occupy
`$FF10–$FF17`; the low address lines A0–A4 select the individual IDE register, and
the 7410 NANDs (U6/U7) combine the page hit with A3/A4 to produce the two True-IDE
chip selects **-CS0** (command block) and **-CS1** (control block). U8 ANDs them
into a single `-CFSEL` "this card is addressed" signal.

### Read / write strobes
DOE code 7 (`-RD`) and DLD code 7 (`-MEMW`) are decoded by U3/U4. Gated with the
clock and `-CFSEL` through U5/U7, they become the IDE bus strobes **-IOR** (I/O
read) and **-IOW** (I/O write) on the connector. These are the standard True-IDE
timing signals the CF card expects.

### Data path
A single **74245** (U1) bridges the P8X data bus and the CF data lines (the low 8
bits — this is 8-bit mode, so the high byte of the IDE 16-bit data path is unused).
Its **direction** follows `-IOR` (read = drive toward the P8X bus) and it is
**enabled** only when the card is selected (`-CFOE`), so it never contends with
other bus drivers.

### Status lines
The CF's open-drain status lines — **IORDY**, **-PDIAG**, **-DASP** — are pulled up
through a SIP resistor network (RN1). `-DASP` (drive active / slave present) also
drives the activity LED.

### Reset
The backplane **-RES** is wired to the IDE connector's reset pin, so the CF card is
reset together with the rest of the machine.

## Bus codes this card owns
- **DOE:** 7 = read (drives D0–D7 when `$FF10–$FF17` is addressed)
- **DLD:** 7 = write (`MEMW`) — shared decode convention with memory & I/O cards

The CF card, memory card, and I/O card all decode the same DOE=7 / DLD=7 codes;
the address decode (which page/region) is what keeps exactly one of them active per
cycle.

## LEDs
PWR (green), ACT (yellow — card selected / access in progress), DASP (green — CF
present and active).

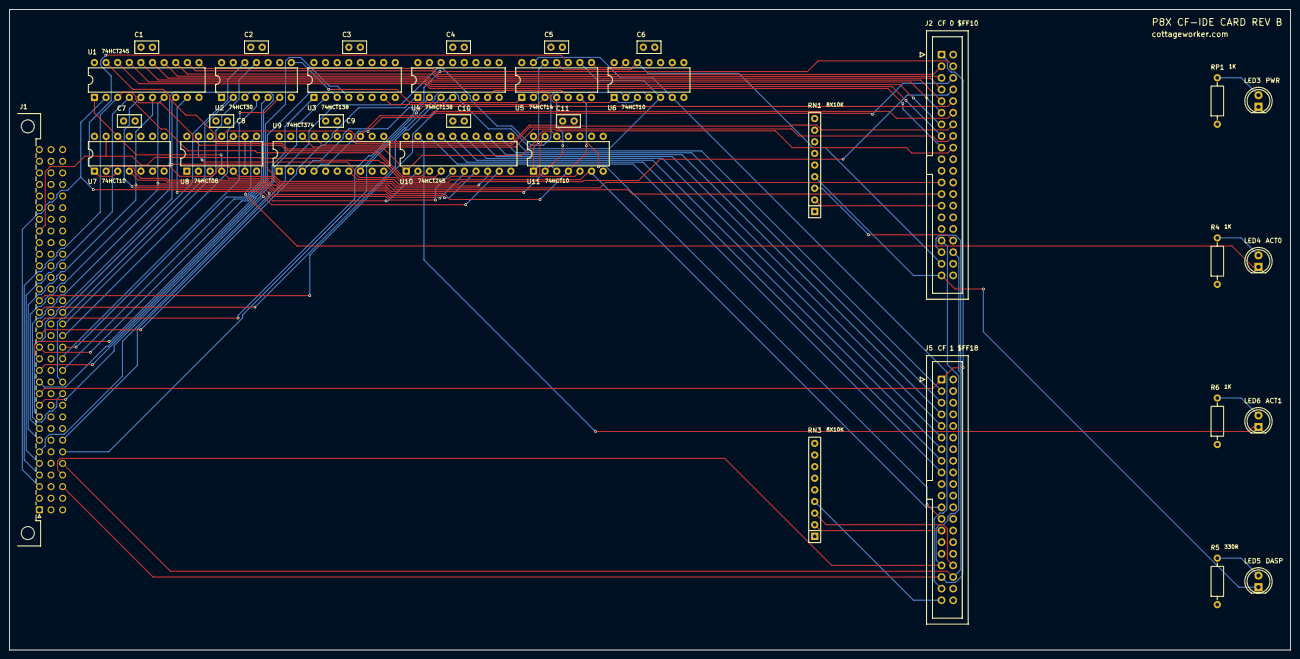
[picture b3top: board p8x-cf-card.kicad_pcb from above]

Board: 4 copper layers, 280.0 x 140.0 mm, 35 parts (0 on the bottom side), 85 nets.

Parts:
C1, C2, C3, C4, C5, C6, C7, C8, C9, C10, C11: 100nF; C_Disc_D5.0mm_W2.5mm_P2.50mm
J1: MABC96R; DIN41612_C_3x32_Male_Horizontal_THT
J2: IDE-40 D0; IDC-Header_2x20_P2.54mm_Vertical
J5: IDE-40 D1; IDC-Header_2x20_P2.54mm_Vertical
LED3, LED5: GRN; LED_D5.0mm
LED4, LED6: YEL; LED_D5.0mm
R4, R6: 1K; R_Axial_DIN0207_L6.3mm_D2.5mm_P10.16mm_Horizontal
R5: 330R; R_Axial_DIN0207_L6.3mm_D2.5mm_P10.16mm_Horizontal
RN1, RN3: 8X10K; R_Array_SIP9
RP1: 1K; R_Axial_DIN0207_L6.3mm_D2.5mm_P10.16mm_Horizontal
U1, U10: 74HCT245; DIP-20_W7.62mm
U2: 74HCT30; DIP-14_W7.62mm
U3, U4: 74HCT138; DIP-16_W7.62mm
U5: 74HCT14; DIP-14_W7.62mm
U6, U7, U11: 74HCT10; DIP-14_W7.62mm
U8: 74HCT08; DIP-14_W7.62mm
U9: 74HCT374; DIP-20_W7.62mm

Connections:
-CFOE: U1.19, U8.6, U8.9, U8.10
-CFOE1: LED6.1, U8.11, U10.19
-CS0: J2.37, U5.11, U6.12
-CS1: J5.37, U5.13, U6.6
-DASP: J2.39, LED5.1, RN1.4
-DASP1: J5.39, RN3.4
-IOR: J2.25, U1.1, U7.12, U8.4
-IOR1: J5.25, U8.12, U10.1, U11.12
-IOW: J2.23, U7.6, U8.5
-IOW1: J5.23, U8.13, U11.6
-MEMW: U4.7, U5.5
-PDIAG: J2.34, RN1.3
-PDIAG1: J5.34, RN3.3
-RD: U3.7, U5.3
-RES: J1.a11, J2.1, J5.1
A0: J1.c3, J2.35, J5.35
A1: J1.c4, J2.33, J5.33
A2: J1.c5, J2.36, J5.36
A3: J1.c6, U5.9, U6.5
A3N: U5.8, U6.13
A4: J1.c7, U6.2, U6.4
A8: J1.c11, U2.1
A9: J1.c12, U2.2
A10: J1.c13, U2.3
A11: J1.c14, U2.4
A12: J1.c15, U2.5
A13: J1.c16, U2.6
A14: J1.c17, U2.11
A15: J1.c18, U2.12
ACTK: LED4.1, U8.8
CF1D0: J5.17, U10.18
CF1D1: J5.15, U10.17
CF1D2: J5.13, U10.16
CF1D3: J5.11, U10.15
CF1D4: J5.9, U10.14
CF1D5: J5.7, U10.13
CF1D6: J5.5, U10.12
CF1D7: J5.3, U10.11
CFD0: J2.17, U1.18
CFD1: J2.15, U1.17
CFD2: J2.13, U1.16
CFD3: J2.11, U1.15
CFD4: J2.9, U1.14
CFD5: J2.7, U1.13
CFD6: J2.5, U1.12
CFD7: J2.3, U1.11
CFD8: J2.4, U9.3
CFD9: J2.6, U9.4
CFD10: J2.8, U9.7
CFD11: J2.10, U9.8
CFD12: J2.12, U9.13
CFD13: J2.14, U9.14
CFD14: J2.16, U9.17
CFD15: J2.18, U9.18
CLKB: J1.a25, U7.5, U7.13, U11.5, U11.13
D0: J1.a3, U1.2, U10.2
D1: J1.a4, U1.3, U10.3
D2: J1.a5, U1.4, U10.4
D3: J1.a6, U1.5, U10.5
D4: J1.a7, U1.6, U10.6
D5: J1.a8, U1.7, U10.7
D6: J1.a9, U1.8, U10.8
D7: J1.a10, U1.9, U10.9
DLD0: J1.a16, U4.1
DLD1: J1.a17, U4.2
DLD2: J1.a18, U4.3
DLD3: J1.a19, U4.4
DOE0: J1.a12, U3.1
DOE1: J1.a13, U3.2
DOE2: J1.a14, U3.3
DOE3: J1.a15, U3.4
GND: C1.2, C2.2, C3.2, C4.2, C5.2, C6.2, C7.2, C8.2, C9.2, C10.2, C11.2, J1.a31, J1.a32, J1.b3, J1.b5, J1.b7, J1.b9, J1.b11, J1.b13, J1.b15, J1.b17, J1.b19, J1.b21, J1.b23, J1.b25, J1.b31, J1.b32, J1.c31, J1.c32, J2.2, J2.19, J2.22, J2.24, J2.26, J2.28, J2.30, J2.40, J5.2, J5.19, J5.22, J5.24, J5.26, J5.28, J5.30, J5.40, LED3.1, U1.10, U2.7, U3.5, U3.8, U4.5, U4.8, U5.7, U6.7, U6.9, U6.10, U6.11, U7.7, U7.9, U7.10, U7.11, U8.1, U8.2, U8.7, U9.10, U9.11, U10.10, U11.7, U11.9, U11.10, U11.11
IOPG: U2.8, U5.1
IOPGP: U5.2, U6.1, U6.3
IORDY: J2.27, RN1.2
IORDY1: J5.27, RN3.2
LEDAC: LED4.2, R4.2
LEDAC1: LED6.2, R6.2
LEDDA: LED5.2, R5.2
LEDP: LED3.2, RP1.2
RDP: U5.4, U7.2, U11.2
SELP: U5.10, U7.1, U7.3
SELP1: U5.12, U11.1, U11.3
VCC: C1.1, C2.1, C3.1, C4.1, C5.1, C6.1, C7.1, C8.1, C9.1, C10.1, C11.1, J1.a1, J1.a2, J1.b1, J1.b2, J1.c1, J1.c2, J2.29, J2.38, J5.29, J5.38, R4.1, R5.1, R6.1, RN1.1, RN3.1, RP1.1, U1.20, U2.14, U3.6, U3.16, U4.6, U4.16, U5.14, U6.14, U7.14, U8.14, U9.1, U9.20, U10.20, U11.14
WRP: U5.6, U7.4, U11.4

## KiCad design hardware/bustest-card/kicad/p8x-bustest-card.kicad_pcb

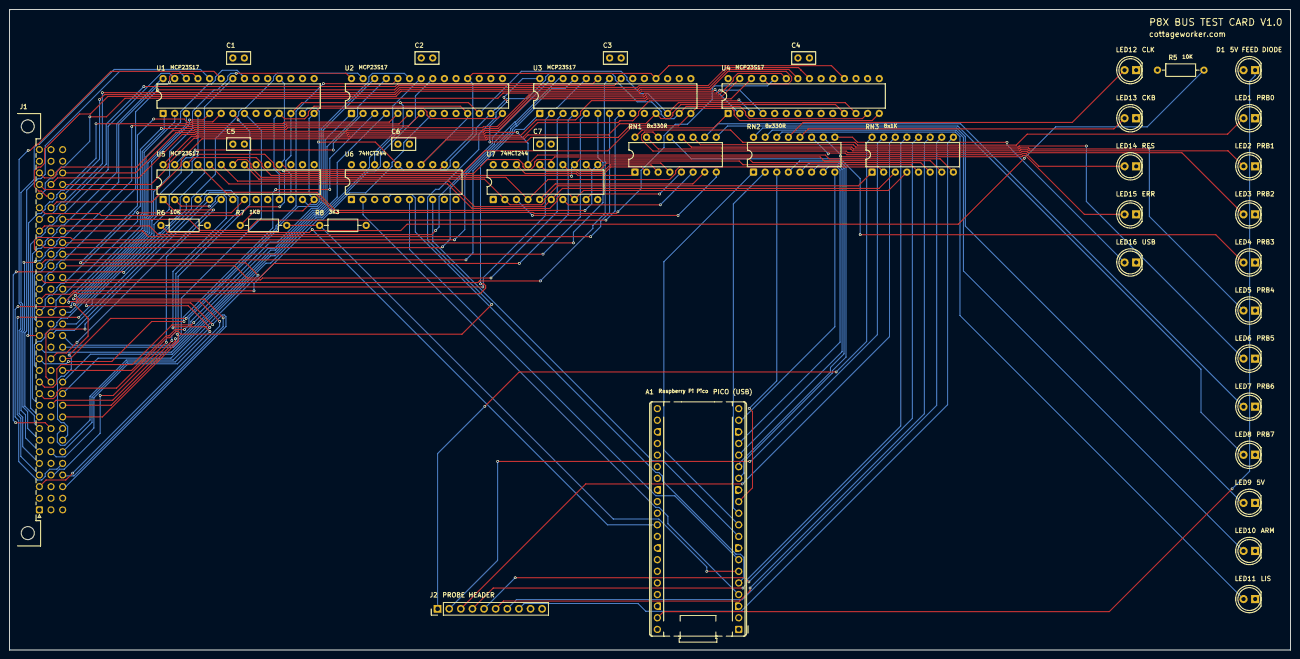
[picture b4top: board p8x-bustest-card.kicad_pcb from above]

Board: 4 copper layers, 280.0 x 140.0 mm, 41 parts (0 on the bottom side), 129 nets.

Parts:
A1: RP2040; RaspberryPi_Pico_Common_THT
C1, C2, C3, C4, C5, C6, C7: 100nF; C_Disc_D5.0mm_W2.5mm_P2.50mm
D1: SCHOTTKY; LED_D5.0mm
J1: MABC96R; DIN41612_C_3x32_Male_Horizontal_THT
J2: PROBE; PinHeader_1x10_P2.54mm_Vertical
LED1: PRB0; LED_D5.0mm
LED2: PRB1; LED_D5.0mm
LED3: PRB2; LED_D5.0mm
LED4: PRB3; LED_D5.0mm
LED5: PRB4; LED_D5.0mm
LED6: PRB5; LED_D5.0mm
LED7: PRB6; LED_D5.0mm
LED8: PRB7; LED_D5.0mm
LED9: 5V; LED_D5.0mm
LED10: ARM; LED_D5.0mm
LED11: LIS; LED_D5.0mm
LED12: CLK; LED_D5.0mm
LED13: CKB; LED_D5.0mm
LED14: RES; LED_D5.0mm
LED15: ERR; LED_D5.0mm
LED16: USB; LED_D5.0mm
R5, R6: 10K; R_Axial_DIN0207_L6.3mm_D2.5mm_P10.16mm_Horizontal
R7: 1K8; R_Axial_DIN0207_L6.3mm_D2.5mm_P10.16mm_Horizontal
R8: 3K3; R_Axial_DIN0207_L6.3mm_D2.5mm_P10.16mm_Horizontal
RN1, RN2: 8x330R; DIP-16_W7.62mm
RN3: 8x1K; DIP-16_W7.62mm
U1, U2, U3, U4, U5: MCP23S17; DIP-28_W7.62mm
U6, U7: 74HCT244; DIP-20_W7.62mm

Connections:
-RES: J1.a11, U3.28
A0: J1.c3, U1.1
A1: J1.c4, U1.2
A2: J1.c5, U1.3
A3: J1.c6, U1.4
A4: J1.c7, U1.5
A5: J1.c8, U1.6
A6: J1.c9, U1.7
A7: J1.c10, U1.8
A8: J1.c11, U2.21
A9: J1.c12, U2.22
A10: J1.c13, U2.23
A11: J1.c14, U2.24
A12: J1.c15, U2.25
A13: J1.c16, U2.26
A14: J1.c17, U2.27
A15: J1.c18, U2.28
ALUM: J1.c23, U3.5
ALUS0: J1.c19, U3.1
ALUS1: J1.c20, U3.2
ALUS2: J1.c21, U3.3
ALUS3: J1.c22, U3.4
BSEL: J1.b28, U4.25
CIN: J1.c24, U3.6
CLK: J1.a24, U3.26
CLKB: J1.a25, U3.27
CLRC: J1.b27, U4.24
CS5: U1.11, U2.11, U3.11, U4.11, U5.11, U6.14
D0: J1.a3, U1.21
D1: J1.a4, U1.22
D2: J1.a5, U1.23
D3: J1.a6, U1.24
D4: J1.a7, U1.25
D5: J1.a8, U1.26
D6: J1.a9, U1.27
D7: J1.a10, U1.28
DLD0: J1.a16, U2.5
DLD1: J1.a17, U2.6
DLD2: J1.a18, U2.7
DLD3: J1.a19, U2.8
DOE0: J1.a12, U2.1
DOE1: J1.a13, U2.2
DOE2: J1.a14, U2.3
DOE3: J1.a15, U2.4
FC: J1.a27, U4.1
FN: J1.a29, U4.3
FV: J1.a30, U4.4
FZ: J1.a28, U4.2
GND: A1.3, A1.8, A1.13, A1.18, A1.23, A1.28, A1.33, A1.38, C1.2, C2.2, C3.2, C4.2, C5.2, C6.2, C7.2, J1.a31, J1.a32, J1.b3, J1.b5, J1.b7, J1.b9, J1.b11, J1.b13, J1.b15, J1.b17, J1.b19, J1.b21, J1.b23, J1.b25, J1.b31, J1.b32, J1.c31, J1.c32, J2.9, J2.10, LED1.1, LED2.1, LED3.1, LED4.1, LED5.1, LED6.1, LED7.1, LED8.1, LED9.1, LED10.1, LED11.1, LED12.1, LED13.1, LED14.1, LED15.1, LED16.1, R6.2, R8.2, U1.10, U1.15, U1.16, U1.17, U1.19, U1.20, U2.10, U2.16, U2.17, U2.19, U2.20, U3.10, U3.15, U3.17, U3.19, U3.20, U4.10, U4.17, U4.19, U4.20, U5.10, U5.15, U5.16, U5.19, U5.20, U6.1, U6.10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
IRQ: J1.b29, U4.27
LDF: J1.a26, U4.21
LDZN: J1.c28, U4.22
LK_PR0: LED1.2, RN1.16
LK_PR1: LED2.2, RN1.15
LK_PR2: LED3.2, RN1.14
LK_PR3: LED4.2, RN1.13
LK_PR4: LED5.2, RN1.12
LK_PR5: LED6.2, RN1.11
LK_PR6: LED7.2, RN1.10
LK_PR7: LED8.2, RN1.9
L_PR0: RN1.1, U7.18
L_PR1: RN1.2, U7.16
L_PR2: RN1.3, U7.14
L_PR3: RN1.4, U7.12
L_PR4: RN1.5, U7.9
L_PR5: RN1.6, U7.7
L_PR6: RN1.7, U7.5
L_PR7: RN1.8, U7.3
P5V: A1.39, D1.1
PDEC: J1.a23, U3.25
PINC: J1.a22, U3.24
PR0: RN3.1, U5.21, U7.2
PR1: RN3.2, U5.22, U7.4
PR2: RN3.3, U5.23, U7.6
PR3: RN3.4, U5.24, U7.8
PR4: RN3.5, U5.25, U7.11
PR5: RN3.6, U5.26, U7.13
PR6: RN3.7, U5.27, U7.15
PR7: RN3.8, U5.28, U7.17
PRJ0: J2.1, RN3.16
PRJ1: J2.2, RN3.15
PRJ2: J2.3, RN3.14
PRJ3: J2.4, RN3.13
PRJ4: J2.5, RN3.12
PRJ5: J2.6, RN3.11
PRJ6: J2.7, RN3.10
PRJ7: J2.8, RN3.9
PSEL0: J1.a20, U3.21
PSEL1: J1.a21, U3.22
PSEL2: J1.c27, U3.23
P_CS: A1.7, U6.6
P_MISO: A1.6, R7.2, R8.1
P_RST: A1.9, U6.8
P_SCK: A1.4, U6.2
P_SI: A1.5, U6.4
RST5: U1.18, U2.18, U3.18, U4.18, U5.18, U6.12
SCK5: U1.12, U2.12, U3.12, U4.12, U5.12, U6.18
SENSE5: A1.31, R5.2, R6.1
SETC: J1.c30, U4.23
SH0: J1.c25, U3.7
SH1: J1.c26, U3.8
SHCIN: J1.c29, U4.26
SI5: U1.13, U2.13, U3.13, U4.13, U5.13, U6.16
SO5: R7.1, U1.14, U2.14, U3.14, U4.14, U5.14
SPARE12: J1.b4, U5.1
SPARE13: J1.b6, U5.2
SPARE14: J1.b8, U5.3
SPARE15: J1.b10, U5.4
SPARE16: J1.b12, U5.5
SPARE17: J1.b14, U5.6
SPARE18: J1.b16, U5.7
SPARE19: J1.b18, U5.8
ST0: A1.10, RN2.1
ST1: A1.11, RN2.2
ST2: A1.12, RN2.3
ST3: A1.14, RN2.4
ST4: A1.15, RN2.5
ST5: A1.16, RN2.6
ST6: A1.17, RN2.7
ST7: A1.19, RN2.8
STK0: LED9.2, RN2.16
STK1: LED10.2, RN2.15
STK2: LED11.2, RN2.14
STK3: LED12.2, RN2.13
STK4: LED13.2, RN2.12
STK5: LED14.2, RN2.11
STK6: LED15.2, RN2.10
STK7: LED16.2, RN2.9
VCC: C1.1, C2.1, C3.1, C4.1, C5.1, C6.1, C7.1, D1.2, J1.a1, J1.a2, J1.b1, J1.b2, J1.c1, J1.c2, R5.1, U1.9, U2.9, U2.15, U3.9, U3.16, U4.9, U4.15, U4.16, U5.9, U5.17, U6.20, U7.20
